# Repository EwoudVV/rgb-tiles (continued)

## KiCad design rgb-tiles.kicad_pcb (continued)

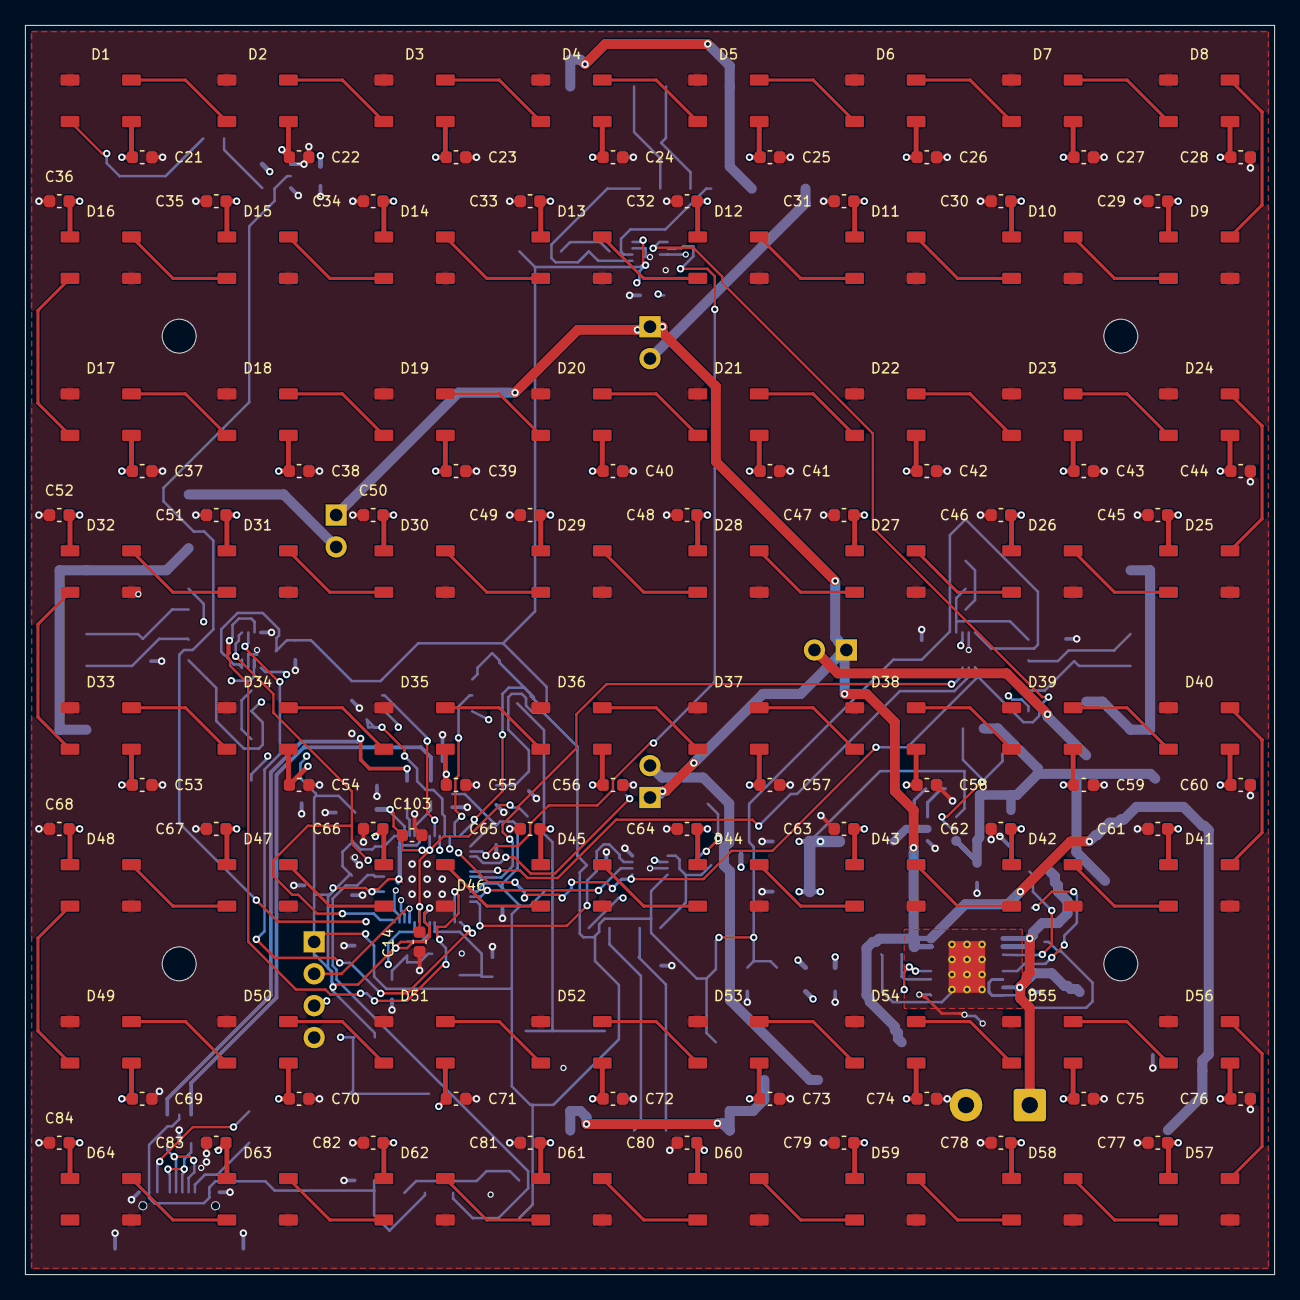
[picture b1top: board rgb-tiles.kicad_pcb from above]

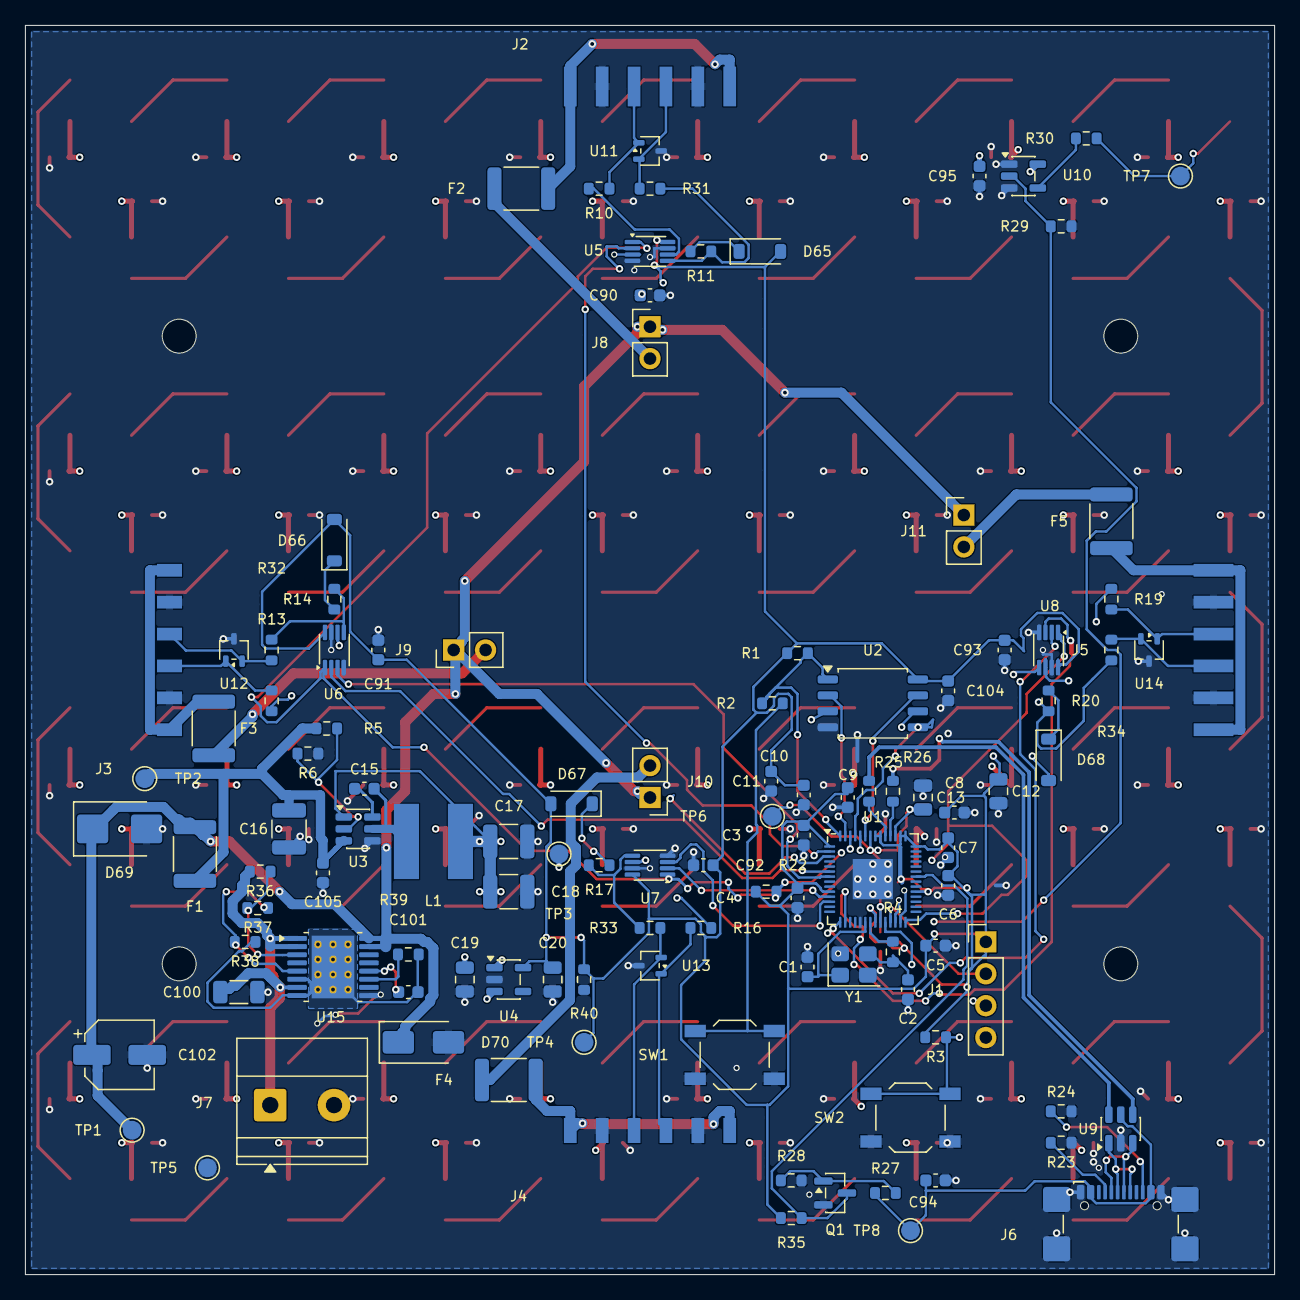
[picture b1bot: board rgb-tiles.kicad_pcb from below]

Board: 4 copper layers, 99.5 x 99.5 mm, 247 parts (113 on the bottom side), 142 nets.

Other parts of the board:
H1, H2, H3, H4: M2.5; MountingHole_2.7mm_M2.5

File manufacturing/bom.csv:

References,Quantity per tile,Value,Manufacturer,MPN,Footprint,Datasheet
"C1, C2",2,15p 50V C0G,KEMET,C0603C150J5GACTU,Capacitor_SMD:C_0603_1608Metric,https://search.kemet.com/component-documentation/download/sp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
C100,1,1u 100V X7R,KEMET,C1206C105K1RACTU,Capacitor_SMD:C_1206_3216Metric,https://search.kemet.com/component-documentation/download/sp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
C101,1,220n 25V X7R,KEMET,C0603C224K3RACTU,Capacitor_SMD:C_0603_1608Metric,https://search.kemet.com/component-documentation/download/sp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
C102,1,47u 25V,Panasonic,EEEFT1E470AR,Capacitor_SMD:CP_Elec_5x5.8,https://industrial.panasonic.com/ww/products/pt/aluminum-cap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
C105,1,100n 50V X7R,KEMET,C0603C104K5RACTU,Capacitor_SMD:C_0603_1608Metric,https://search.kemet.com/component-documentation/download/sp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
"C12, C13",2,2.2u 16V X7R,KEMET,C0805C225K4RACTU,Capacitor_SMD:C_0805_2012Metric,https://search.kemet.com/component-documentation/download/sp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
C16,1,10u 50V X7R,Samsung Electro-Mechanics,CL32B106KBJNNNE,Capacitor_SMD:C_1210_3225Metric,https://product.samsungsem.com/mlcc/CL32B106KBJNNN.do
"C17, C18",2,22u 25V X7R,Samsung Electro-Mechanics,CL32B226KAJNNNE,Capacitor_SMD:C_1210_3225Metric,https://product.samsungsem.com/mlcc/CL32B226KAJNNN.do
"C19, C20",2,4.7u 16V X7R,KEMET,C0805C475K4RACTU,Capacitor_SMD:C_0805_2012Metric,https://search.kemet.com/component-documentation/download/sp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
"C3, C4, C5, C6, C7, C8, C9, C10, C11, C14, C103, C104, C21, C22, C23, C24, C25, C26, C27, C28, C29, C30, C31, C32, C33, C34, C35, C36, C37, C38, C39, C40, C41, C42, C43, C44, C45, C46, C47, C48, C49, C50, C51, C52, C53, C54, C55, C56, C57, C58, C59, C60, C61, C62, C63, C64, C65, C66, C67, C68, C69, C70, C71, C72, C73, C74, C75, C76, C77, C78, C79, C80, C81, C82, C83, C84, C15, C90, C91, C92, C93, C94, C95",83,100n 25V X7R,Samsung Electro-Mechanics,CL10B104KA8NNNC,Capacitor_SMD:C_0603_1608Metric,https://product.samsungsem.com/mlcc/CL10B104KA8NNN.do
"D1, D2, D3, D4, D5, D6, D7, D8, D9, D10, D11, D12, D13, D14, D15, D16, D17, D18, D19, D20, D21, D22, D23, D24, D25, D26, D27, D28, D29, D30, D31, D32, D33, D34, D35, D36, D37, D38, D39, D40, D41, D42, D43, D44, D45, D46, D47, D48, D49, D50, D51, D52, D53, D54, D55, D56, D57, D58, D59, D60, D61, D62, D63, D64",64,WS2812C-V6,Worldsemi,WS2812C-V6,RGB_Tiles:LED_WS2812C-V6_5050_SteppedCourtyard,https://datasheet.lcsc.com/datasheet/pdf/805ce88c7337e0c0370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
"D65, D66, D67, D68",4,1N4148W-7-F,Diodes Incorporated,1N4148W-7-F,Diode_SMD:D_SOD-123,https://www.diodes.com/datasheet/download/1N4148W.pdf
D69,1,SMBJ13A,Diodes Incorporated,SMBJ13A-13-F,Diode_SMD:D_SMB,https://www.diodes.com/part/view/SMBJ13A
D70,1,B340A,Diodes Incorporated,B340A-13-F,Diode_SMD:D_SMA,https://www.diodes.com/datasheet/download/B340A.pdf
"F1, F2, F3, F4, F5",5,1812L150/24MR,Littelfuse,1812L150/24MR,Fuse:Fuse_1812_4532Metric,https://www.littelfuse.com/~/media/electronics/datasheets/re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
J1,1,SWD,Samtec,TSW-104-07-T-S,Connector_PinHeader_2.54mm:PinHeader_1x04_P2.54mm_Vertical,https://suddendocs.samtec.com/prints/tsw-xxx-xx-xxx-x-xx-xxx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
J10,1,S POWER LINK,CJT,A2541WV-2P,Connector_PinHeader_2.54mm:PinHeader_1x02_P2.54mm_Vertical,https://www.cjt.com/upload/A2541.pdf
J11,1,W POWER LINK,CJT,A2541WV-2P,Connector_PinHeader_2.54mm:PinHeader_1x02_P2.54mm_Vertical,https://www.cjt.com/upload/A2541.pdf
J2,1,N / M20-8890645R,Harwin,M20-8890645R,RGB_Tiles:Harwin_M20-8890645R_1x06_RA_SMD,https://www.harwin.com/products/M20-8890645R
J3,1,E / M20-7910642R,Harwin,M20-7910642R,RGB_Tiles:Harwin_M20-7910642R_1x06_RA_SMD,https://www.harwin.com/products/M20-7910642R
J4,1,S / M20-7910642R,Harwin,M20-7910642R,RGB_Tiles:Harwin_M20-7910642R_1x06_RA_SMD,https://www.harwin.com/products/M20-7910642R
J5,1,W / M20-8890645R,Harwin,M20-8890645R,RGB_Tiles:Harwin_M20-8890645R_1x06_RA_SMD,https://www.harwin.com/products/M20-8890645R
J6,1,USB4110-GF-A,GCT,USB4110-GF-A,Connector_USB:USB_C_Receptacle_GCT_USB4110,https://gct.co/download?name=USB4110.pdf&type=PDFDrawing
J7,1,12V INPUT,Phoenix Contact,1715721,"TerminalBlock_Phoenix:TerminalBlock_Phoenix_MKDS-1,5-2-5.08_1x02_P5.08mm_Horizontal",https://www.phoenixcontact.com/en-il/products/printed-circui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
J8,1,N POWER LINK,CJT,A2541WV-2P,Connector_PinHeader_2.54mm:PinHeader_1x02_P2.54mm_Vertical,https://www.cjt.com/upload/A2541.pdf
J9,1,E POWER LINK,CJT,A2541WV-2P,Connector_PinHeader_2.54mm:PinHeader_1x02_P2.54mm_Vertical,https://www.cjt.com/upload/A2541.pdf
L1,1,SRN6045-4R7Y 4.7uH,Bourns,SRN6045-4R7Y,RGB_Tiles:L_Bourns_SRN6045,https://www.bourns.com/docs/product-datasheets/srn6045.pdf
Q1,1,AO3400A,Alpha & Omega Semiconductor,AO3400A,Package_TO_SOT_SMD:SOT-23,https://www.aosmd.com/sites/default/files/res/datasheets/AO3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
"R1, R3, R11, R14, R17, R20, R22, R35",8,10k,Yageo,RC0603FR-0710KL,Resistor_SMD:R_0603_1608Metric,
"R10, R13, R16, R19",4,220,Yageo,RC0603FR-07220RL,Resistor_SMD:R_0603_1608Metric,
"R2, R4",2,1k,Yageo,RC0603FR-071KL,Resistor_SMD:R_0603_1608Metric,
"R23, R24",2,5.1k,Yageo,RC0603FR-075K1L,Resistor_SMD:R_0603_1608Metric,
"R25, R26",2,27,Yageo,RC0603FR-0727RL,Resistor_SMD:R_0603_1608Metric,
"R27, R29",2,100k,Yageo,RC0603FR-07100KL,Resistor_SMD:R_0603_1608Metric,
R28,1,1M,Yageo,RC0603FR-071ML,Resistor_SMD:R_0603_1608Metric,
"R31, R32, R33, R34, R30",5,100,Yageo,RC0603FR-07100RL,Resistor_SMD:R_0603_1608Metric,
R36,1,100k 1%,Yageo,RC0603FR-07100KL,Resistor_SMD:R_0603_1608Metric,
R37,1,3.32k 1%,Yageo,RC0603FR-073K32L,Resistor_SMD:R_0603_1608Metric,
R38,1,10k 1%,Yageo,RC0603FR-0710KL,Resistor_SMD:R_0603_1608Metric,
R39,1,6.04k 1%,Yageo,RC0603FR-076K04L,Resistor_SMD:R_0603_1608Metric,
R40,1,2.2k,Yageo,RC0603FR-072K2L,Resistor_SMD:R_0603_1608Metric,
R5,1,27.4k 1%,Yageo,RC0603FR-0727K4L,Resistor_SMD:R_0603_1608Metric,
R6,1,3.6k 1%,Yageo,RC0603FR-133K6L,Resistor_SMD:R_0603_1608Metric,https://www.yageo.com/upload/media/product/productsearch/dat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
SW1,1,BOOT,E-Switch,TL3342F160QG,Button_Switch_SMD:SW_SPST_TL3342,https://www.e-switch.com/product/tl3342-series-low-profile-s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
SW2,1,RESET,E-Switch,TL3342F160QG,Button_Switch_SMD:SW_SPST_TL3342,https://www.e-switch.com/product/tl3342-series-low-profile-s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
U1,1,RP2040,Raspberry Pi,RP2040,Package_DFN_QFN:QFN-56-1EP_7x7mm_P0.4mm_EP3.2x3.2mm,https://datasheets.raspberrypi.com/rp2040/rp2040-datasheet.pdf
U10,1,SN74AHCT1G125DBVR,Texas Instruments,SN74AHCT1G125DBVR,Package_TO_SOT_SMD:SOT-23-5,https://www.ti.com/lit/ds/symlink/sn74ahct1g125.pdf
"U11, U12, U13, U14",4,TPD2E2U06QDCKRQ1,Texas Instruments,TPD2E2U06QDCKRQ1,Package_TO_SOT_SMD:SOT-323_SC-70,https://www.ti.com/lit/ds/symlink/tpd2e2u06-q1.pdf
U15,1,TPS26600PWPR,Texas Instruments,TPS26600PWPR,RGB_Tiles:HTSSOP16_EP_4.4x5_P0.65_Vias0.3,https://www.ti.com/lit/ds/symlink/tps2660.pdf
U2,1,W25Q16JVSSIQ,Winbond,W25Q16JVSSIM,Package_SO:SOIC-8_5.3x5.3mm_P1.27mm,https://www.winbond.com/resource-files/w25q16jv%20spi%20revg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
U3,1,AP63205WU-7,Diodes Incorporated,AP63205WU-7,Package_TO_SOT_SMD:TSOT-23-6,https://www.diodes.com/datasheet/download/AP63200-AP63201-AP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
U4,1,AP2112K-3.3TRG1,Diodes Incorporated,AP2112K-3.3TRG1,Package_TO_SOT_SMD:SOT-23-5,https://www.diodes.com/datasheet/download/AP2112.pdf
"U5, U6, U7, U8",4,SN74LVC2G125DCUR,Texas Instruments,SN74LVC2G125DCUR,Package_SO:VSSOP-8_2.3x2mm_P0.5mm,https://www.ti.com/lit/ds/symlink/sn74lvc2g125.pdf
U9,1,USBLC6-2SC6,STMicroelectronics,USBLC6-2SC6,Package_TO_SOT_SMD:SOT-23-6,https://www.st.com/resource/en/datasheet/usblc6-2.pdf
Y1,1,ABM8-272-T3 12MHz,Abracon,ABM8-272-T3,Crystal:Crystal_SMD_3225-4Pin_3.2x2.5mm,https://abracon.com/datasheets/ABM8-272-T3.pdf
"Shunts for J8, J9, J10, J11",4,2.54mm removable power shunt,Samtec,SNT-100-BK-T,"Accessory, no PCB footprint",https://suddendocs.samtec.com/catalog_english/snt.pdf
